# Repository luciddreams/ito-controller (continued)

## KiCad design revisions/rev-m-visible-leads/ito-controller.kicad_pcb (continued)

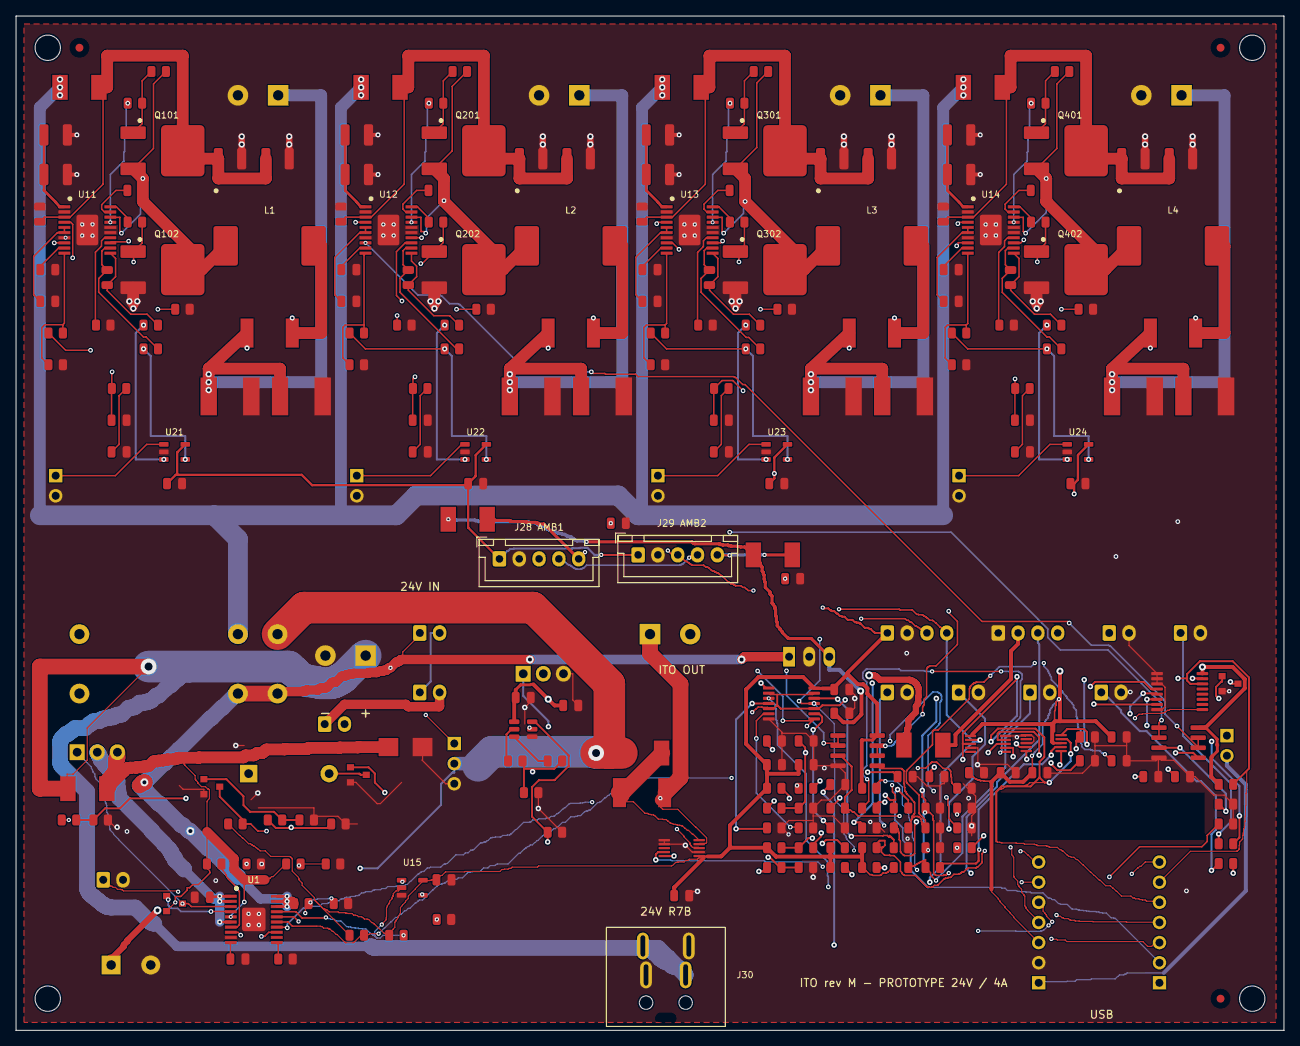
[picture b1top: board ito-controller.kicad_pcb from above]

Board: 4 copper layers, 160.0 x 128.0 mm, 269 parts (0 on the bottom side), 155 nets.

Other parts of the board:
FID1, FID2, FID3: Fiducial 1mm; Fiducial_1mm_Mask2mm
H1, H2, H3, H4: MountingHole_3.2mm

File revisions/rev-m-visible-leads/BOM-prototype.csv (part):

Reference,Quantity,Value,Description_EN,Manufacturer,MPN,Footprint,Specification,Assembly,Fit
J1,1,XIAO right socket 1x7 - USB down,"Top view, module components up, USB down: J1 at right; D0 pin1 bottom.",Samtec,SSW-107-01-G-S,ITO_PCB:PinSocket_1x07_P2.54mm_Vertical,,Check footprint,FIT
J2,1,XIAO left socket 1x7 - USB down,"Top view, module components up, USB down: J2 at left; 5V pin1 bottom.",Samtec,SSW-107-01-G-S,ITO_PCB:PinSocket_1x07_P2.54mm_Vertical,,Check footprint,FIT
M1,1,TSR 1-2450,"5 V / 1 A, input 6.5–36 V; SIP3 IN-GND-OUT 2.54mm verified. Keep JP1 open when USB supplies MCU.",TRACO Power,TSR 1-2450,ITO_PCB:Converter_DCDC_TRACO_TSR-1_THT,,SMD,FIT
JP1,1,Voedingsjumper - standaard OPEN,Alleen sluiten zonder USB-VBUS; geen automatische bronselectie.,Samtec,TSW-102-07-G-S,ITO_PCB:PinHeader_1x02_P2.54mm_Vertical,,Check footprint,FIT
C1,1,10u / 10V,,Murata,GRM21BR61E106KA73L,ITO_PCB:C_0805_2012Metric,"0805, 10uF, 25V, X5R, 10%; used on <=5V rails",SMD,FIT
C2,1,10u / 10V,,Murata,GRM21BR61E106KA73L,ITO_PCB:C_0805_2012Metric,"0805, 10uF, 25V, X5R, 10%; used on <=5V rails",SMD,FIT
R1,1,2k2,I2C pull-up; start at100kHz and measure rise time.,Yageo,RC0805FR-072K2L,ITO_PCB:R_0805_2012Metric,"0805, 1%, >=0.125W, >=50V",SMD,FIT
R2,1,2k2,I2C pull-up; start at100kHz and measure rise time.,Yageo,RC0805FR-072K2L,ITO_PCB:R_0805_2012Metric,"0805, 1%, >=0.125W, >=50V",SMD,FIT
R3,1,10k,,Yageo,RC0805FR-0710KL,ITO_PCB:R_0805_2012Metric,"0805, 1%, >=0.125W, >=50V",SMD,FIT
J5,1,Connector 2 pins,"Externe drukknop, normaal open.",JST,B2B-XH-A(LF)(SN),ITO_PCB:JST_XH_B2B-XH-A_1x02_P2.50mm_Vertical,,Check footprint,FIT
R4,1,0R,Links eFuse IMON to ADC load/filter.,Yageo,RC0805JR-070RL,ITO_PCB:R_0805_2012Metric,0805 zero-ohm link; signal only,SMD,FIT
R5,1,10k 0.1%,IMON load: nominal 0.279V/A; calibrate before closed-loop current budget.,Yageo,RT0805BRD0710KL,ITO_PCB:R_0805_2012Metric,"0805 thin film, 0.1%, 25ppm/K or better, >=0.125W",SMD,FIT
R6,1,1k,,Yageo,RC0805FR-071KL,ITO_PCB:R_0805_2012Metric,"0805, 1%, >=0.125W, >=50V",SMD,FIT
C3,1,100n,,Murata,GRM21BR71H104KA01L,ITO_PCB:C_0805_2012Metric,"0805, 100nF, 50V, X7R, 10%",SMD,FIT
R7,1,4k7,Strong TEC_ARM reset pulldown; absorbs UCC27511 IN- internal pullup current.,Yageo,RC0805FR-074K7L,ITO_PCB:R_0805_2012Metric,"0805, 1%, >=0.125W, >=50V",SMD,FIT
J3,1,Connector 2 pins,"Mean Well GST160A24-R7B; J3:1 +24V, J3:2 return; prototype 4A operating budget.",Phoenix Contact,1715721,"ITO_PCB:TerminalBlock_Phoenix_MKDS-1,5-2-5.08_1x02_P5.08mm_Horizontal","MKDS 1,5/2-5,08; 2 positions, pitch 5.08mm",Check footprint,FIT
F1,1,10A / 125V DC 0451010.MRL,"10 A, 125 VDC series. 25% continuous-current derating plus temperature rerating. NOT a precise current limiter; supply short-circuit behavior and pulse I2t must be coordinated.",Littelfuse,0451010.MRL,ITO_PCB:Littelfuse_451,,SMD,FIT
D1,1,SMBJ33CA bidirectioneel,"See PROTOTYPE-START.md, ASSEMBLY.md and BOM specification.",Littelfuse,SMBJ33CA,ITO_PCB:D_SMB,,SMD,FIT
U1,1,TPS26631PWPR,MODE open = latch-off. 4.5 A nominal sustained limit. TPS26631 permits 2x current pulse after PGOOD for nominal 25.5 ms; not fault-identical to TPS26630.,Texas Instruments,TPS26631PWPR,ITO_PCB:TI_PWP0020T_EP2.96,TPS26631PWPR,SMD,FIT
R10,1,156k 0.1%,,Yageo,RT0805BRD07156KL,ITO_PCB:R_0805_2012Metric,"0805 thin film, 0.1%, 25ppm/K or better, >=0.125W",SMD,FIT
R11,1,10k 0.1%,,Yageo,RT0805BRD0710KL,ITO_PCB:R_0805_2012Metric,"0805 thin film, 0.1%, 25ppm/K or better, >=0.125W",SMD,FIT
R12,1,223k 0.1%,,Yageo,RT0805BRD07223KL,ITO_PCB:R_0805_2012Metric,"0805 thin film, 0.1%, 25ppm/K or better, >=0.125W",SMD,FIT
R13,1,10k 0.1%,,Yageo,RT0805BRD0710KL,ITO_PCB:R_0805_2012Metric,"0805 thin film, 0.1%, 25ppm/K or better, >=0.125W",SMD,FIT
R14,1,4.02k 0.1%,,Yageo,RT0805BRD074K02L,ITO_PCB:R_0805_2012Metric,"0805 thin film, 0.1%, 25ppm/K or better, >=0.125W",SMD,FIT
R15,1,10k,,Yageo,RC0805FR-0710KL,ITO_PCB:R_0805_2012Metric,"0805, 1%, >=0.125W, >=50V",SMD,FIT
Q2,1,IRLB4030PBF,"100V blocking FET, G-D-S; 4.5mOhm max at4.5V gate. Gate ramp handled by TPS26631; no external linear soft-start.",Infineon,IRLB4030PBF,ITO_PCB:TO-220-3_Vertical,,SMD,FIT
Q3,1,BSS138LT1G,External blocking FET fast turn-off.,onsemi,BSS138LT1G,ITO_PCB:SOT-23,,SMD,FIT
R16,1,150k 0.1%,,Yageo,RT0805BRD07150KL,ITO_PCB:R_0805_2012Metric,"0805 thin film, 0.1%, 25ppm/K or better, >=0.125W",SMD,FIT
R17,1,10k 0.1%,,Yageo,RT0805BRD0710KL,ITO_PCB:R_0805_2012Metric,"0805 thin film, 0.1%, 25ppm/K or better, >=0.125W",SMD,FIT
R18,1,1k,,Yageo,RC0805FR-071KL,ITO_PCB:R_0805_2012Metric,"0805, 1%, >=0.125W, >=50V",SMD,FIT
C4,1,100n / 50V X7R 10%,X7R timing part selected; startup calculation includes wider capacitance allowance.,Murata,GRM21BR71H104KA01L,ITO_PCB:C_0805_2012Metric,"dVdt timing; calculate with effective C = 70..127nF, including temperature/aging allowance",SMD,FIT
C5,1,470u / 50V EEUFR1H471,Bulk after active eFuse; not additional to candidate stage bulk.,Panasonic,EEUFR1H471,ITO_PCB:CP_Radial_D12.5mm_P5.00mm,"470uF 50V radial; 12.5mm diameter, 5mm pitch; reserve22mm height",SMD,FIT
C6,1,1u / 50V X7R,,Murata,GRM21BR71H105KA12L,ITO_PCB:C_0805_2012Metric,"0805, 1uF, 50V, X7R, 10%",SMD,FIT
J6,1,Connector 2 pins,"Vergrendelende noodstop, NC contact, geschikt voor 24V DC spoelkring.",JST,B2B-XH-A(LF)(SN),ITO_PCB:JST_XH_B2B-XH-A_1x02_P2.50mm_Vertical,,Check footprint,FIT
J7,1,Connector 2 pins,"See PROTOTYPE-START.md, ASSEMBLY.md and BOM specification.",JST,B2B-XH-A(LF)(SN),ITO_PCB:JST_XH_B2B-XH-A_1x02_P2.50mm_Vertical,,Check footprint,FIT
J8,1,Connector 2 pins,"See PROTOTYPE-START.md, ASSEMBLY.md and BOM specification.",JST,B2B-XH-A(LF)(SN),ITO_PCB:JST_XH_B2B-XH-A_1x02_P2.50mm_Vertical,,Check footprint,FIT
K1,1,G2RL-1A-E DC24,"See PROTOTYPE-START.md, ASSEMBLY.md and BOM specification.",Omron,G2RL-1A-E DC24,ITO_PCB:G2RL_1A_E_review,,Check footprint,FIT
D2,1,1N4007,Vrijloopdiode direct over spoel; verlengt afvaltijd.,Vishay,1N4007-E3/54,ITO_PCB:D_DO-41_SOD81_P10.16mm_Horizontal,,SMD,FIT
Q4,1,MMBT3904,,onsemi,MMBT3904LT1G,ITO_PCB:SOT-23,,SMD,FIT
R20,1,2k2,,Yageo,RC0805FR-072K2L,ITO_PCB:R_0805_2012Metric,"0805, 1%, >=0.125W, >=50V",SMD,FIT
R21,1,100k,,Yageo,RC0805FR-07100KL,ITO_PCB:R_0805_2012Metric,"0805, 1%, >=0.125W, >=50V",SMD,FIT
Q5,1,MMBT3904,,onsemi,MMBT3904LT1G,ITO_PCB:SOT-23,,SMD,FIT
R22,1,100k,,Yageo,RC0805FR-07100KL,ITO_PCB:R_0805_2012Metric,"0805, 1%, >=0.125W, >=50V",SMD,FIT
R23,1,100k,,Yageo,RC0805FR-07100KL,ITO_PCB:R_0805_2012Metric,"0805, 1%, >=0.125W, >=50V",SMD,FIT
R24,1,10k,,Yageo,RC0805FR-0710KL,ITO_PCB:R_0805_2012Metric,"0805, 1%, >=0.125W, >=50V",SMD,FIT
R25,1,10k / 0.25W,Ontladen en gedefinieerde uit-status. Terugmelding heeft wachttijd nodig.,Panasonic,ERJP06F1002V,ITO_PCB:R_0805_2012Metric,"0805 10k 1%, 0.5W; output bleeder.",SMD,FIT
TP1,1,Connector 3 pins,"Meetpunten; LOAD_PRESENT_N laag betekent spanning aanwezig, geen gecertificeerde contactbewaking.",Samtec,TSW-103-07-G-S,ITO_PCB:PinHeader_1x03_P2.54mm_Vertical,,SMD,FIT
F2,1,5A / 125V DC 0451005.MRL,"5 A, 125 VDC series. 25% continuous-current derating plus temperature rerating. NOT a precise current limiter; supply short-circuit behavior and pulse I2t must be coordinated.",Littelfuse,0451005.MRL,ITO_PCB:Littelfuse_451,,SMD,FIT
RSH1,1,10m / 1W / 1% WSL2512R0100FEA,"1 W at 70 C, 1%, component TCR 75 ppm/K. Pads 1.65 x 3.68 mm, inner gap 4.06 mm. Kelvin topology must be checked after footprint change.",Vishay,WSL2512R0100FEA,ITO_PCB:WSL2512_7m_to_500m,,SMD,FIT
J4,1,Connector 2 pins,"See PROTOTYPE-START.md, ASSEMBLY.md and BOM specification.",Phoenix Contact,1715721,"ITO_PCB:TerminalBlock_Phoenix_MKDS-1,5-2-5.08_1x02_P5.08mm_Horizontal","MKDS 1,5/2-5,08; 2 positions, pitch 5.08mm",Check footprint,FIT
Q1,1,STP55NF06L,"Drain ook op metalen tab; circa 0.22W bij 3.33A, Rds 20m bij 5V en 25C.",STMicroelectronics,STP55NF06L,ITO_PCB:TO-220-3_Vertical,,SMD,FIT
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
